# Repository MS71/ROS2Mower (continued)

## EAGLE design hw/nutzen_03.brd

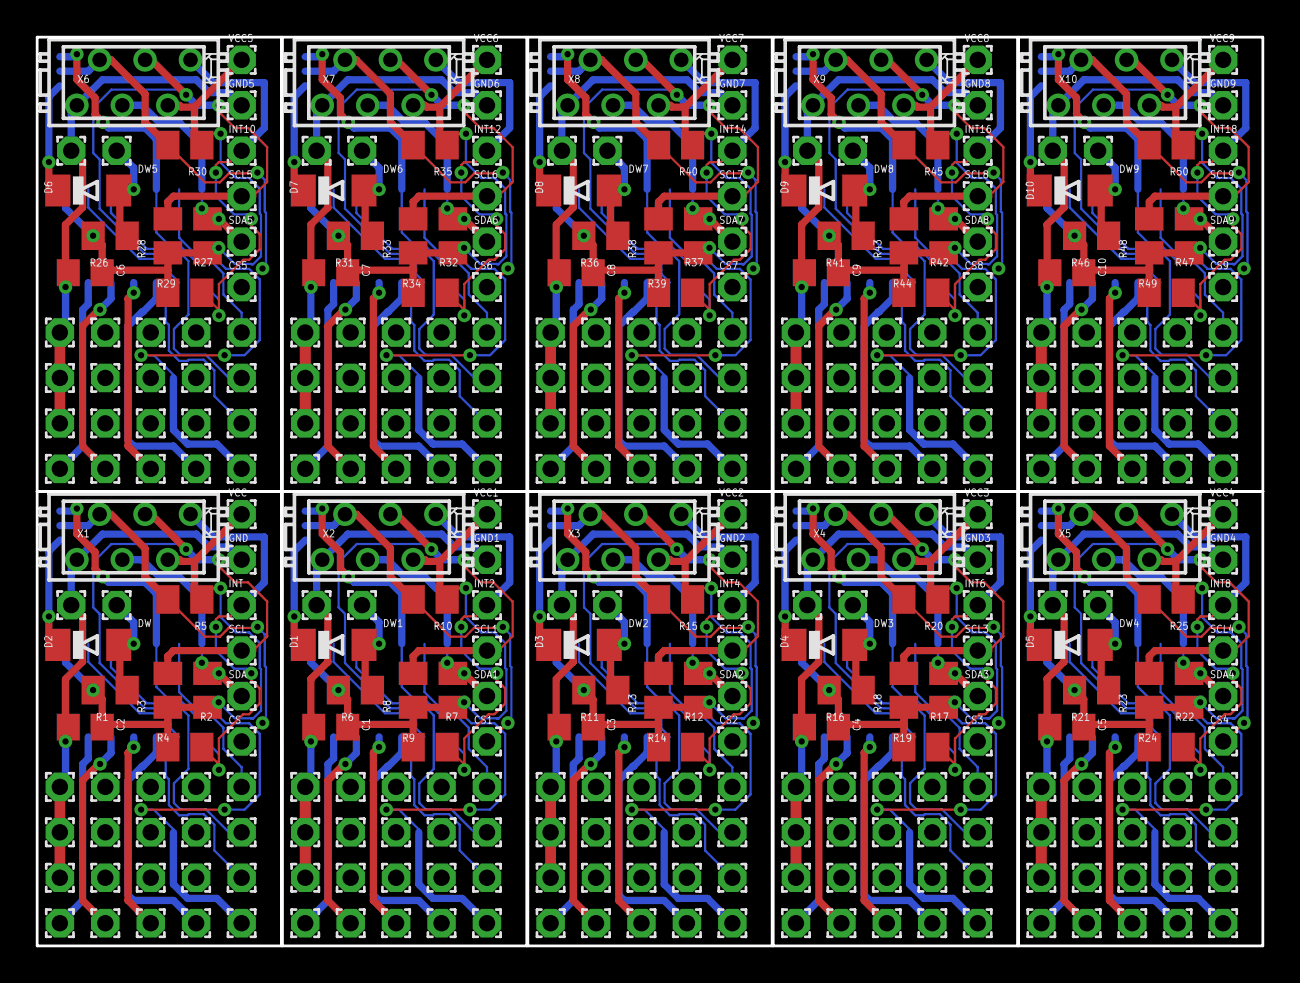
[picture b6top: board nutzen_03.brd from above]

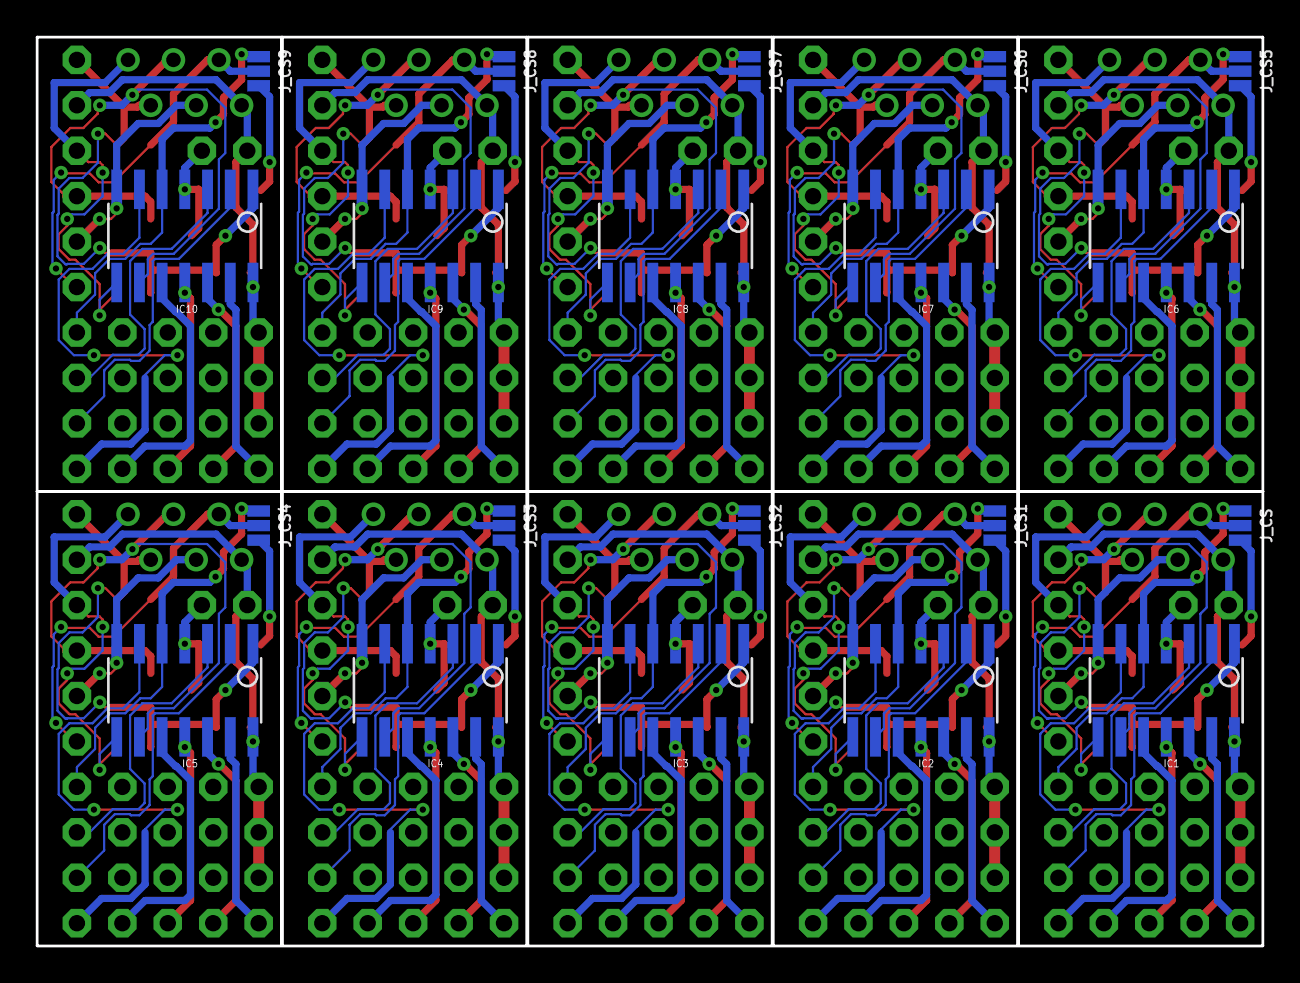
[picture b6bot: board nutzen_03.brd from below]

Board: 2 copper layers, 68.5 x 50.8 mm, 380 parts (20 on the bottom side), 160 nets.

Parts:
C1, C2, C3, C4, C5, C6, C7, C8, C9, C10: 100n; C0805
CS, CS1, CS2, CS3, CS4, CS5, CS6, CS7, CS8, CS9: 1,6/0,9
D1, D2, D3, D4, D5, D6, D7, D8, D9, D10: MINIMELF
DW, DW1, DW2, DW3, DW4, DW5, DW6, DW7, DW8, DW9: 1,6/0,9
GND, GND1, GND2, GND3, GND4, GND5, GND6, GND7, GND8, GND9: 1,6/0,9
GND_, GND_1, GND_2, GND_3, GND_4, GND_5, GND_6, GND_7, GND_8, GND_9: 1,6/0,9
IC1, IC2, IC3, IC4, IC5, IC6, IC7, IC8, IC9, IC10: TINY84 or TINY841; SOIC14
INT, INT0, INT1, INT2, INT3, INT4, INT5, INT6, INT7, INT8, INT9, INT10, INT11, INT12, INT13, INT14, INT15, INT16, INT17, INT18: 1,6/0,9
J_CS, J_CS1, J_CS2, J_CS3, J_CS4, J_CS5, J_CS6, J_CS7, J_CS8, J_CS9: SMT-JUMPER_3_1-NC_PASTE_NO-SILK
PA0, PA1, PA2, PA3, PA4, PA5, PA6, PA7, PA8, PA9, PA10, PA11, PA12, PA13, PA14, PA15, PA16, PA17, PA18, PA19, PA20, PA21, PA22, PA23, PA24, PA25, PA26, PA27, PA28, PA29, PA30, PA31, PA32, PA33, PA34, PA35, PA36, PA37, PA38, PA39, PA40, PA41, PA42, PA43, PA44, PA45, PA46, PA47, PA48, PA49: 1,6/0,9
PAD1, PAD2, PAD3, PAD4, PAD5, PAD6, PAD7, PAD8, PAD9, PAD10, PAD11, PAD12, PAD13, PAD14, PAD15, PAD16, PAD17, PAD18, PAD19, PAD20, PAD21, PAD22, PAD23, PAD24, PAD25, PAD26, PAD27, PAD28, PAD29, PAD30, PAD31, PAD32, PAD33, PAD34, PAD35, PAD36, PAD37, PAD38, PAD39, PAD40, PAD41, PAD42, PAD43, PAD44, PAD45, PAD46, PAD47, PAD48, PAD49, PAD50, PAD51, PAD52, PAD53, PAD54, PAD55, PAD56, PAD57, PAD58, PAD59, PAD60, PAD61, PAD62, PAD63, PAD64, PAD65, PAD66, PAD67, PAD68, PAD69, PAD70, PAD71, PAD72, PAD73, PAD74, PAD75, PAD76, PAD77, PAD78, PAD79, PAD80, PAD81, PAD82, PAD83, PAD84, PAD85, PAD86, PAD87, PAD88, PAD89, PAD90, PAD91, PAD92, PAD93, PAD94, PAD95, PAD96, PAD97, PAD98, PAD99, PAD100, PAD101, PAD102, PAD103, PAD104, PAD105, PAD106, PAD107, PAD108, PAD109, PAD110, PAD111, PAD112, PAD113, PAD114, PAD115, PAD116, PAD117, PAD118, PAD119, PAD120: 1,6/0,9
PB0, PB1, PB2, PB3, PB4, PB5, PB6, PB7, PB8, PB9, PB10, PB11, PB12, PB13, PB14, PB15, PB16, PB17, PB18, PB19: 1,6/0,9
R1, R2, R3, R4, R5, R6, R7, R8, R9, R10, R11, R12, R13, R14, R15, R16, R17, R18, R19, R20, R21, R22, R23, R24, R25, R26, R27, R28, R29, R30, R31, R32, R33, R34, R35, R36, R37, R38, R39, R40, R41, R42, R43, R44, R45, R46, R47, R48, R49, R50: 10k; M0805
SCL, SCL1, SCL2, SCL3, SCL4, SCL5, SCL6, SCL7, SCL8, SCL9: 1,6/0,9
SDA, SDA1, SDA2, SDA3, SDA4, SDA5, SDA6, SDA7, SDA8, SDA9: 1,6/0,9
VCC, VCC1, VCC2, VCC3, VCC4, VCC5, VCC6, VCC7, VCC8, VCC9: 1,6/0,9
X1, X2, X3, X4, X5, X6, X7, X8, X9, X10: BUS; MICROMATCH-6

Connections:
BUS_INT: IC1.8, INT.1, R4.2, X1.1
BUS_INT1: IC2.8, INT2.1, R9.2, X2.1
BUS_INT2: IC3.8, INT4.1, R14.2, X3.1
BUS_INT3: IC4.8, INT6.1, R19.2, X4.1
BUS_INT4: IC5.8, INT8.1, R24.2, X5.1
BUS_INT5: IC6.8, INT10.1, R29.2, X6.1
BUS_INT6: IC7.8, INT12.1, R34.2, X7.1
BUS_INT7: IC8.8, INT14.1, R39.2, X8.1
BUS_INT8: IC9.8, INT16.1, R44.2, X9.1
BUS_INT9: IC10.8, INT18.1, R49.2, X10.1
BUS_P1: CS1.1, J_CS1.2, R10.2, X2.5
BUS_P2: CS2.1, J_CS2.2, R15.2, X3.5
BUS_P3: CS3.1, J_CS3.2, R20.2, X4.5
BUS_P4: CS4.1, J_CS4.2, R25.2, X5.5
BUS_P5: CS.1, J_CS.2, R5.2, X1.5
BUS_P6: CS5.1, J_CS5.2, R30.2, X6.5
BUS_P7: CS6.1, J_CS6.2, R35.2, X7.5
BUS_P8: CS7.1, J_CS7.2, R40.2, X8.5
BUS_P9: CS8.1, J_CS8.2, R45.2, X9.5
BUS_P10: CS9.1, J_CS9.2, R50.2, X10.5
BUS_RESET: D2.C, J_CS.3
BUS_RESET1: D1.C, J_CS1.3
BUS_RESET2: D3.C, J_CS2.3
BUS_RESET3: D4.C, J_CS3.3
BUS_RESET4: D5.C, J_CS4.3
BUS_RESET5: D6.C, J_CS5.3
BUS_RESET6: D7.C, J_CS6.3
BUS_RESET7: D8.C, J_CS7.3
BUS_RESET8: D9.C, J_CS8.3
BUS_RESET9: D10.C, J_CS9.3
BUS_SCL: IC1.9, R3.2, SCL.1, X1.3
BUS_SCL1: IC2.9, R8.2, SCL1.1, X2.3
BUS_SCL2: IC3.9, R13.2, SCL2.1, X3.3
BUS_SCL3: IC4.9, R18.2, SCL3.1, X4.3
BUS_SCL4: IC5.9, R23.2, SCL4.1, X5.3
BUS_SCL5: IC6.9, R28.2, SCL5.1, X6.3
BUS_SCL6: IC7.9, R33.2, SCL6.1, X7.3
BUS_SCL7: IC8.9, R38.2, SCL7.1, X8.3
BUS_SCL8: IC9.9, R43.2, SCL8.1, X9.3
BUS_SCL9: IC10.9, R48.2, SCL9.1, X10.3
BUS_SDA: IC1.7, R2.2, SDA.1, X1.4
BUS_SDA1: IC2.7, R7.2, SDA1.1, X2.4
BUS_SDA2: IC3.7, R12.2, SDA2.1, X3.4
BUS_SDA3: IC4.7, R17.2, SDA3.1, X4.4
BUS_SDA4: IC5.7, R22.2, SDA4.1, X5.4
BUS_SDA5: IC6.7, R27.2, SDA5.1, X6.4
BUS_SDA6: IC7.7, R32.2, SDA6.1, X7.4
BUS_SDA7: IC8.7, R37.2, SDA7.1, X8.4
BUS_SDA8: IC9.7, R42.2, SDA8.1, X9.4
BUS_SDA9: IC10.7, R47.2, SDA9.1, X10.4
DW: D2.A, DW.1, IC1.4, R1.2
DW1: D1.A, DW1.1, IC2.4, R6.2
DW2: D3.A, DW2.1, IC3.4, R11.2
DW3: D4.A, DW3.1, IC4.4, R16.2
DW4: D5.A, DW4.1, IC5.4, R21.2
DW5: D6.A, DW5.1, IC6.4, R26.2
DW6: D7.A, DW6.1, IC7.4, R31.2
DW7: D8.A, DW7.1, IC8.4, R36.2
DW8: D9.A, DW8.1, IC9.4, R41.2
DW9: D10.A, DW9.1, IC10.4, R46.2
GND: C2.2, GND.1, GND_.1, IC1.14, PAD100.1, PAD101.1, PAD102.1, X1.6
GND1: C1.2, GND1.1, GND_1.1, IC2.14, PAD10.1, PAD11.1, PAD12.1, X2.6
GND2: C3.2, GND2.1, GND_2.1, IC3.14, PAD22.1, PAD23.1, PAD24.1, X3.6
GND3: C4.2, GND3.1, GND_3.1, IC4.14, PAD34.1, PAD35.1, PAD36.1, X4.6
GND4: C5.2, GND4.1, GND_4.1, IC5.14, PAD46.1, PAD47.1, PAD48.1, X5.6
GND5: C6.2, GND5.1, GND_5.1, IC6.14, PAD58.1, PAD59.1, PAD60.1, X6.6
GND6: C7.2, GND6.1, GND_6.1, IC7.14, PAD70.1, PAD71.1, PAD72.1, X7.6
GND7: C8.2, GND7.1, GND_7.1, IC8.14, PAD82.1, PAD83.1, PAD84.1, X8.6
GND8: C9.2, GND8.1, GND_8.1, IC9.14, PAD106.1, PAD107.1, PAD108.1, X9.6
GND9: C10.2, GND9.1, GND_9.1, IC10.14, PAD118.1, PAD119.1, PAD120.1, X10.6
INT0: IC1.5, INT0.1, J_CS.1
INT1: IC2.5, INT1.1, J_CS1.1
INT2: IC3.5, INT3.1, J_CS2.1
INT3: IC4.5, INT5.1, J_CS3.1
INT4: IC5.5, INT7.1, J_CS4.1
INT5: IC6.5, INT9.1, J_CS5.1
INT6: IC7.5, INT11.1, J_CS6.1
INT7: IC8.5, INT13.1, J_CS7.1
INT8: IC9.5, INT15.1, J_CS8.1
INT9: IC10.5, INT17.1, J_CS9.1
PA0: IC1.13, PA0.1
PA1: IC1.12, PA1.1
PA2: IC1.11, PA2.1
PA3: IC1.10, PA3.1
PA4: IC2.13, PA4.1
PA5: IC2.6, PA9.1
PA6: IC2.10, PA8.1
PA7: IC1.6, PA7.1
PA8: IC2.11, PA6.1
PA9: IC2.12, PA5.1
PA10: IC3.13, PA10.1
PA11: IC3.6, PA14.1
PA12: IC3.10, PA13.1
PA13: IC3.11, PA12.1
PA14: IC3.12, PA11.1
PA15: IC4.13, PA15.1
PA16: IC4.6, PA19.1
PA17: IC4.10, PA18.1
PA18: IC4.11, PA17.1
PA19: IC4.12, PA16.1
PA20: IC5.13, PA20.1
PA21: IC5.6, PA24.1
PA22: IC5.10, PA23.1
PA23: IC5.11, PA22.1
PA24: IC5.12, PA21.1
PA25: IC6.13, PA25.1
PA26: IC6.6, PA29.1
PA27: IC6.10, PA28.1
PA28: IC6.11, PA27.1
PA29: IC6.12, PA26.1
PA30: IC7.13, PA30.1
PA31: IC7.6, PA34.1
PA32: IC7.10, PA33.1
PA33: IC7.11, PA32.1
PA34: IC7.12, PA31.1
PA35: IC8.13, PA35.1
PA36: IC8.6, PA39.1
PA37: IC8.10, PA38.1
PA38: IC8.11, PA37.1
PA39: IC8.12, PA36.1
PA40: IC9.13, PA40.1
PA41: IC9.6, PA44.1
PA42: IC9.10, PA43.1
PA43: IC9.11, PA42.1
PA44: IC9.12, PA41.1
PA45: IC10.13, PA45.1
PA46: IC10.6, PA49.1
PA47: IC10.10, PA48.1
PA48: IC10.11, PA47.1
PA49: IC10.12, PA46.1
PB0: IC1.2, PB0.1
PB1: IC1.3, PB1.1
PB2: IC2.3, PB3.1
PB3: IC2.2, PB2.1
PB4: IC3.3, PB5.1
PB5: IC3.2, PB4.1
PB6: IC4.3, PB7.1
PB7: IC4.2, PB6.1
PB8: IC5.3, PB9.1
PB9: IC5.2, PB8.1
PB10: IC6.3, PB11.1
PB11: IC6.2, PB10.1
PB12: IC7.3, PB13.1
PB13: IC7.2, PB12.1
PB14: IC8.3, PB15.1
PB15: IC8.2, PB14.1
PB16: IC9.3, PB17.1
PB17: IC9.2, PB16.1
PB18: IC10.3, PB19.1
PB19: IC10.2, PB18.1
VCC: C2.1, IC1.1, R1.1, R2.1, R3.1, R4.1, R5.1, VCC.1, X1.2
VCC1: C1.1, IC2.1, R6.1, R7.1, R8.1, R9.1, R10.1, VCC1.1, X2.2
VCC2: C3.1, IC3.1, R11.1, R12.1, R13.1, R14.1, R15.1, VCC2.1, X3.2
VCC3: C4.1, IC4.1, R16.1, R17.1, R18.1, R19.1, R20.1, VCC3.1, X4.2
VCC4: C5.1, IC5.1, R21.1, R22.1, R23.1, R24.1, R25.1, VCC4.1, X5.2
VCC5: C6.1, IC6.1, R26.1, R27.1, R28.1, R29.1, R30.1, VCC5.1, X6.2
VCC6: C7.1, IC7.1, R31.1, R32.1, R33.1, R34.1, R35.1, VCC6.1, X7.2
VCC7: C8.1, IC8.1, R36.1, R37.1, R38.1, R39.1, R40.1, VCC7.1, X8.2
VCC8: C9.1, IC9.1, R41.1, R42.1, R43.1, R44.1, R45.1, VCC8.1, X9.2
VCC9: C10.1, IC10.1, R46.1, R47.1, R48.1, R49.1, R50.1, VCC9.1, X10.2
